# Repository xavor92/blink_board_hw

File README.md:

# BLINK BOARD

## Basic Info

## Libraries

Create a folder called libraries

Extract the following libraries:

* https://github.com/Basirk/kicad-ESP8266
* https://github.com/pforrmi/KiCad-SSD1306-128x64

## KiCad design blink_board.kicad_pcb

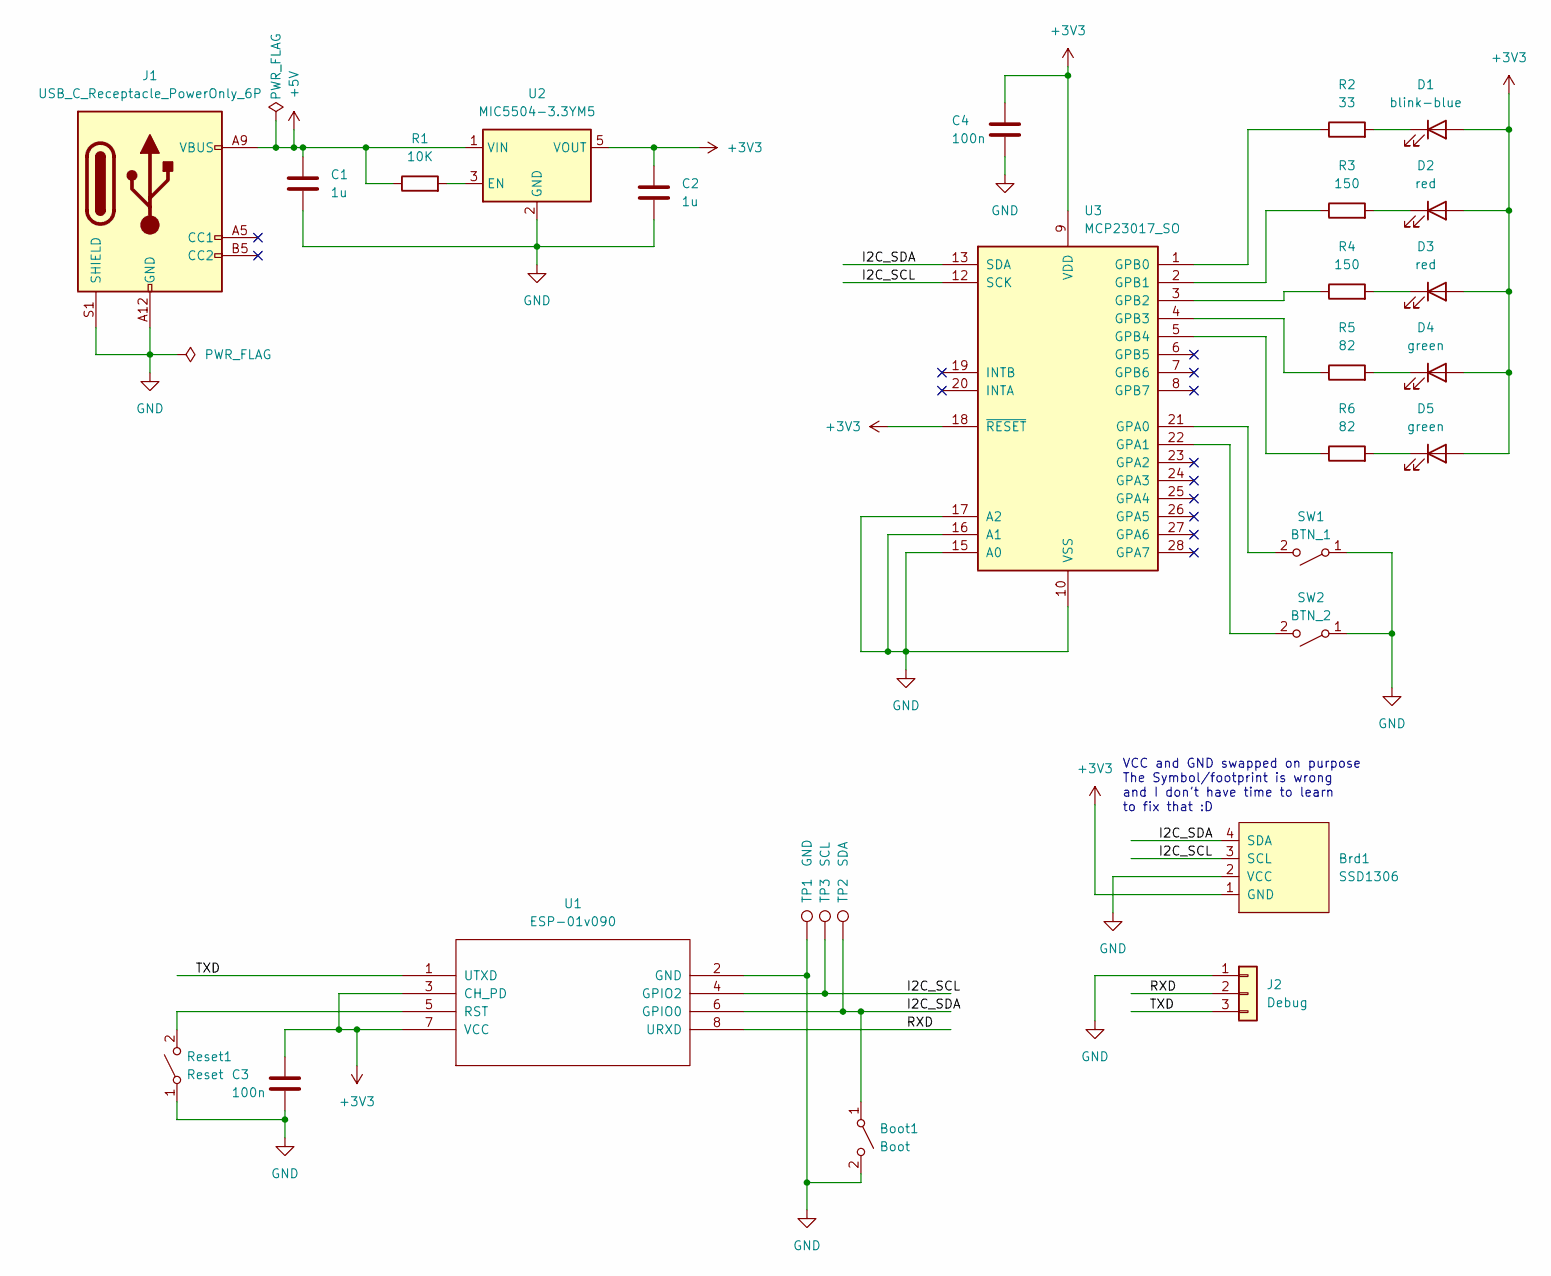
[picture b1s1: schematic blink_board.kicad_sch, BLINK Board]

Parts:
Boot1: Boot; SW_Push_1P1T_NO_6x6mm_H9.5mm; Mouser 179-TS046650BK100SMT
Brd1: SSD1306; 128x64OLED
C1, C2: 1u; C_0805_2012Metric_Pad1.18x1.45mm_HandSolder; Mouser 963-UMK212B7105KG-T
C3, C4: 100n; C_0805_2012Metric_Pad1.18x1.45mm_HandSolder; Mouser 581-KGM21NR71H104KT
D1: blink-blue; LED_0805_2012Metric_Pad1.15x1.40mm_HandSolder; Mouser 710-150080BS75000
D2, D3: red; LED_0805_2012Metric_Pad1.15x1.40mm_HandSolder; Mouser 710-150080RS75000
D4, D5: green; LED_0805_2012Metric_Pad1.15x1.40mm_HandSolder; Mouser 710-150080GS75000
J1: USB_C_Receptacle_PowerOnly_6P; USB_C_Receptacle_GCT_USB4125-xx-x_6P_TopMnt_Horizontal; Mouser 649-10164359-00011LF
J2: Debug; PinHeader_1x03_P2.54mm_Vertical
R1: 10K; R_0805_2012Metric_Pad1.20x1.40mm_HandSolder; Mouser 71-CRCW0805-10K-E3
R2: 33; R_0805_2012Metric_Pad1.20x1.40mm_HandSolder; Mouser 71-CRCW080533R0JNEAC
R3, R4: 150; R_0805_2012Metric_Pad1.20x1.40mm_HandSolder; Mouser 71-CRCW0805150RFKEAC
R5, R6: 82; R_0805_2012Metric_Pad1.20x1.40mm_HandSolder; Mouser 71-CRCW0805J-82-E3
Reset1: Reset; SW_Push_1P1T_NO_6x6mm_H9.5mm; Mouser 179-TS046650BK100SMT
SW1: BTN_1; SW_Push_1P1T_NO_6x6mm_H9.5mm; Mouser 179-TS046650BK100SMT
SW2: BTN_2; SW_Push_1P1T_NO_6x6mm_H9.5mm; Mouser 179-TS046650BK100SMT
TP1: GND; TestPoint_Pad_D1.5mm
TP2: SDA; TestPoint_Pad_D1.5mm
TP3: SCL; TestPoint_Pad_D1.5mm
U1: ESP-01v090; ESP-01; Mouser 910-HDR100IMP40FGVTH
U2: MIC5504-3.3YM5; SOT-23-5_HandSoldering; Mouser 998-MIC5504-3.3YM5TR
U3: MCP23017_SO; SOIC-28W_7.5x17.9mm_P1.27mm; Mouser 579-MCP23017-E/SO

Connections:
+3V3: Brd1.1 (GND), C2.1, C3.1, C4.1, D1.2 (A), D2.2 (A), D3.2 (A), D4.2 (A), D5.2 (A), U1.3 (CH_PD), U1.7 (VCC), U2.5 (VOUT), U3.9 (VDD), U3.18 (~RESET)
+5V: C1.1, J1.A9 (VBUS), J1.B9 (VBUS), R1.1, U2.1 (VIN)
/I2C_SCL: Brd1.3 (SCL), TP3.1, U1.4 (GPIO2), U3.12 (SCK)
/I2C_SDA: Boot1.1 (A), Brd1.4 (SDA), TP2.1, U1.6 (GPIO0), U3.13 (SDA)
/RXD: J2.2, U1.8 (URXD)
/TXD: J2.3, U1.1 (UTXD)
GND: Boot1.2 (B), Brd1.2 (VCC), C1.2, C2.2, C3.2, C4.2, J1.A12 (GND), J1.B12 (GND), J1.S1 (SHIELD), J2.1, Reset1.1 (A), SW1.1 (A), SW2.1 (A), TP1.1, U1.2 (GND), U2.2 (GND), U3.10 (VSS), U3.15 (A0), U3.16 (A1), U3.17 (A2)
unnamed: D1.1 (K), R2.2
unnamed: D2.1 (K), R3.2
unnamed: D3.1 (K), R4.2
unnamed: D4.1 (K), R5.2
unnamed: D5.1 (K), R6.2
unnamed: Reset1.2 (B), U1.5 (RST)
unnamed: SW1.2 (B), U3.21 (GPA0)
unnamed: SW2.2 (B), U3.22 (GPA1)
unnamed: R1.2, U2.3 (EN)
unnamed: R2.1, U3.1 (GPB0)
unnamed: R3.1, U3.2 (GPB1)
unnamed: R4.1, U3.3 (GPB2)
unnamed: R5.1, U3.4 (GPB3)
unnamed: R6.1, U3.5 (GPB4)

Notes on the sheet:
VCC and GND swapped on purpose The Symbol/footprint is wrong and I don't have time to learn to fix that :D

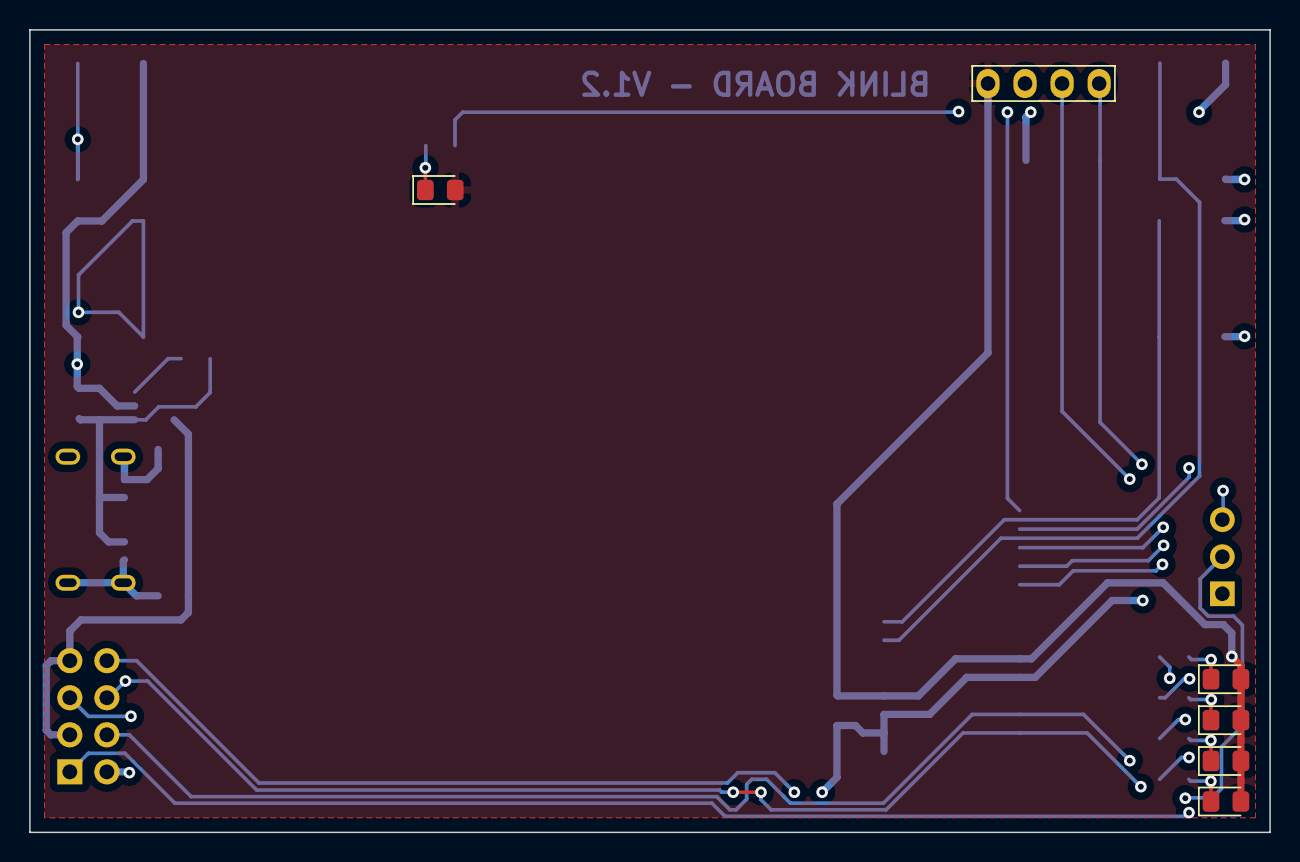
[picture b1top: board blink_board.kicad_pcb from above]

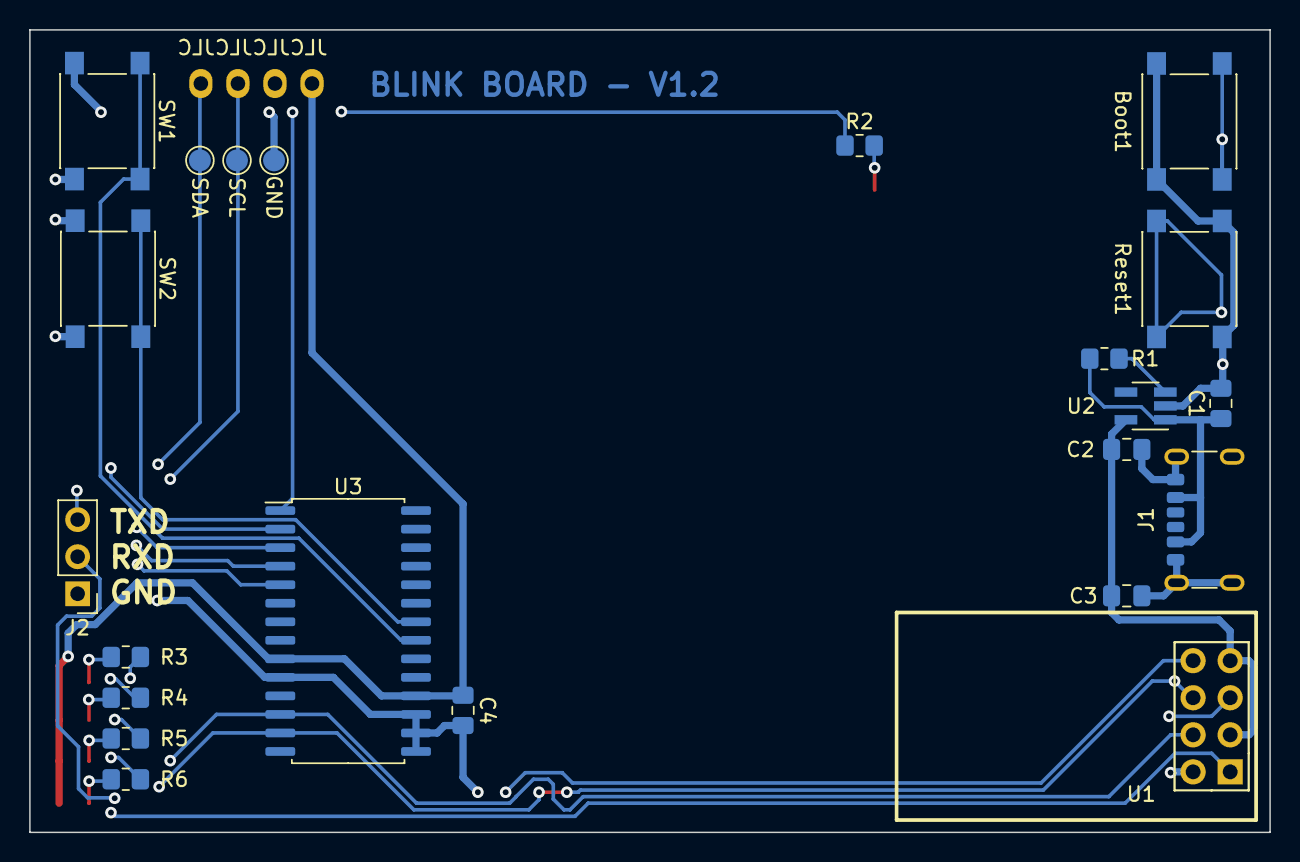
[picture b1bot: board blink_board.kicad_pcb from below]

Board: 4 copper layers, 85.0 x 55.0 mm, 28 parts (22 on the bottom side), 21 nets.

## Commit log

2023-12-04 Initial commit of V1.5
2023-12-04 Add notes for V2
2023-12-04 add more notes, update gitignore
2023-12-06 Bugfixes and updates
    * Added small board description
    * Added testpads for I2C
    * Fixed power for display
    * Added labels for Serial
    * Aligned buttons
    * Cleaned silkscreen
2023-12-13 Add Layout info
